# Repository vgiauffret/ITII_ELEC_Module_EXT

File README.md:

# ITII_ELEC_Module_EXT
Notre projet consiste à améliorer une ruche d’abeille en y ajoutant des capteurs pour permettre à un apiculteur d’obtenir différentes informations sur son ruché tel que la température, l’humidité et le poids de la ruche.

Toutes ces améliorations de la ruche ne doivent en aucun cas gêner l’apiculteur dans son travail et doivent permettre à la ruche de rester mobile. Le système doit être autonome.

Nous sommes en charges de créer le module externe de la Ruche. Le but du module externe de la ruche connecté est de gérer, d'enregistrer la visite de l'apiculteur et de transmettre les données relatives à l'entretien des ruches à une gateway. Le module devra fournir une IHM pour permettre à l'apiculteur d'interagir avec le système et de plusieurs capteurs permettant de récupérer les informations désirées.

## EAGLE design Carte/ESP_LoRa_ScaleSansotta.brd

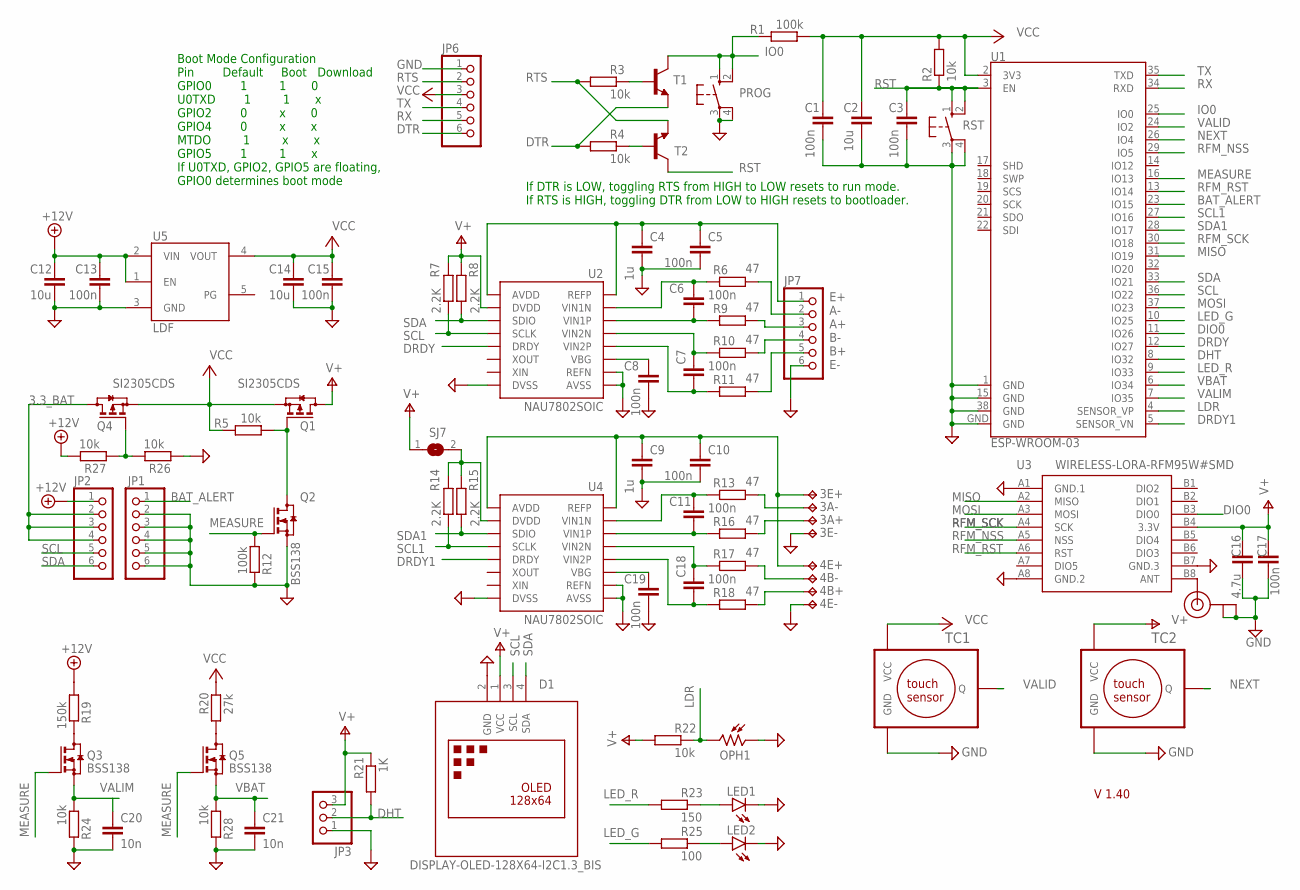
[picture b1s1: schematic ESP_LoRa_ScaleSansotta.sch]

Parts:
3A+, 3A-, 3E+, 3E-, 4B+, 4B-, 4E+, 4E-: TPTP17SQ; TP17SQ
C1, C3, C5, C6, C7, C8, C10, C11, C13, C15, C17, C18, C19: 100n; C1206
C2, C12, C14: 10u; C1210
C4, C9: 1u; C1210
C16: 4.7u; C1210
C20, C21: 10n; C1206
D1: DISPLAY-OLED-128X64-I2C1.3_BIS; DISPLAY-OLED-128X64-1.3-I2C_BIS
J1: U.FL
JP1, JP2, JP6, JP7: PINHD-1X6; 1X06
JP3: PINHD-1X3; 1X03
LED1, LED2: LEDSMT1206; 1206
OPH1: VT93N2; VT900
PROG: 10-XX; B3F-10XX
Q1, Q4: SI2305CDS; SOT23
Q2, Q3, Q5: BSS138; SOT23
R1, R12: 100k; R1206
R2, R3, R4, R5, R22, R24, R26, R27, R28: 10k; R1206
R6, R9, R10, R11, R13, R16, R17, R18: 47; R1206
R7, R8, R14, R15: 2.2K; R1206
R19: 150k; R1206
R20: 27k; R1206
R21: 1K; R1206
R23: 150; R1206
R25: 100; R1206
RST: 10-XX; B3F-10XX
SJ7: SJ
T1, T2: MMBT2222ALT1-NPN-SOT23-BEC; SOT23-BEC
TC1, TC2: TTP223R_H; TTP233RED_H
U1: ESP-WROOM-03
U2, U4: NAU7802SOIC; SO16
U3: WIRELESS-LORA-RFM95W#SMD
U5: LDF3.3; PPAK

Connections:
3.3_BAT: JP2.2, JP2.3, JP2.4, Q4.3 (D)
+12V: C12.1, C13.1, JP2.1, R19.1, R27.2, U5.1 (EN), U5.2 (VIN)
BAT_ALERT: JP1.1, U1.23 (IO15)
DHT: JP3.2, R21.1, U1.8 (IO32)
DIO0: U1.11 (IO26), U3.B3 (DIO0)
DRDY: U1.12 (IO27), U2.12 (DRDY)
DRDY1: U1.5 (SENSOR_VN), U4.12 (DRDY)
DTR: JP6.6, R4.1, T1.E
GND: 3E-.TP, 4E-.TP, C1.2, C2.2, C3.2, C4.2, C5.2, C8.2, C9.2, C10.2, C12.2, C13.2, C14.2, C15.2, C16.2, C17.2, C19.2, C20.2, C21.2, D1.2 (GND), J1.1 (GND), J1.2 (GND), JP1.2, JP1.3, JP1.4, JP1.5, JP1.6, JP3.1, JP6.1, JP7.6, LED1.C, LED2.C, OPH1.1, PROG.3, PROG.4 (P1), Q2.2 (S), R12.2, R24.2, R26.1, R28.2, RST.3, RST.4 (P1), TC1.P$3 (GND), TC2.P$3 (GND), U1.1 (GND), U1.15 (GND), U1.38 (GND), U1.GND, U2.7 (REFN), U2.8 (AVSS), U2.9 (DVSS), U3.A1 (GND.1), U3.A8 (GND.2), U3.B7 (GND.3), U4.7 (REFN), U4.8 (AVSS), U4.9 (DVSS), U5.3 (GND)
IO0: PROG.1 (S), PROG.2 (S1), R1.2, T1.C, U1.25 (IO0)
LDR: OPH1.2, R22.2, U1.4 (SENSOR_VP)
LED_G: R25.1, U1.10 (IO25)
LED_R: R23.1, U1.9 (IO33)
MEASURE: Q2.1 (G), Q3.1 (G), Q5.1 (G), R12.1, U1.16 (IO13)
MISO: U1.31 (IO19), U3.A2 (MISO)
MOSI: U1.37 (IO23), U3.A3 (MOSI)
unnamed: Q1.1 (G), Q2.3 (D), R5.1
unnamed: Q3.3 (D), R19.2
unnamed: J1.3 (SIGNAL), U3.B8 (ANT)
unnamed: R14.2, R15.2, SJ7.2, U4.15 (DVDD)
unnamed: Q5.3 (D), R20.1
unnamed: LED1.A, R23.2
unnamed: LED2.A, R25.2
unnamed: R3.2, T1.B
unnamed: JP7.2, R6.2
unnamed: R4.2, T2.B
unnamed: C8.1, U2.6 (VBG)
unnamed: C19.1, U4.6 (VBG)
unnamed: C11.2, R16.1, U4.3 (VIN1P)
unnamed: C11.1, R13.1, U4.2 (VIN1N)
unnamed: C6.2, R9.1, U2.3 (VIN1P)
unnamed: C6.1, R6.1, U2.2 (VIN1N)
unnamed: C7.1, R10.1, U2.4 (VIN2N)
unnamed: C7.2, R11.1, U2.5 (VIN2P)
unnamed: JP7.3, R9.2
unnamed: JP7.5, R11.2
unnamed: JP7.4, R10.2
unnamed: C18.1, R17.1, U4.4 (VIN2N)
unnamed: C18.2, R18.1, U4.5 (VIN2P)
unnamed: 4B+.TP, R18.2
unnamed: 4B-.TP, R17.2
unnamed: 3E+.TP, 4E+.TP, C9.1, C10.1, U4.1 (REFP), U4.16 (AVDD)
unnamed: 3A-.TP, R13.2
unnamed: 3A+.TP, R16.2
unnamed: C4.1, C5.1, JP7.1, U2.1 (REFP), U2.16 (AVDD)
unnamed: Q4.1 (G), R26.2, R27.1
NEXT: TC2.P$2 (Q), U1.26 (IO4)
RFM_NSS: U1.29 (IO5), U3.A5 (NSS)
RFM_RST: U1.13 (IO14), U3.A6 (RST)
RFM_SCK: U1.30 (IO18), U3.A4 (SCK)
RST: C3.1, R2.1, RST.1 (S), RST.2 (S1), T2.C, U1.3 (EN)
RTS: JP6.2, R3.1, T2.E
RX: JP6.5, U1.34 (RXD)
SCL: D1.3 (SCL), JP2.5, R7.1, U1.36 (IO22), U2.13 (SCLK)
SCL1: R14.1, U1.27 (IO16), U4.13 (SCLK)
SDA: D1.4 (SDA), JP2.6, R8.1, U1.33 (IO21), U2.14 (SDIO)
SDA1: R15.1, U1.28 (IO17), U4.14 (SDIO)
TX: JP6.4, U1.35 (TXD)
V+: C16.1, C17.1, D1.1 (VCC), JP3.3, Q1.3 (D), R7.2, R8.2, R21.2, R22.1, SJ7.1, TC2.P$1 (VCC), U2.15 (DVDD), U3.B4 (3.3V)
VALID: TC1.P$2 (Q), U1.24 (IO2)
VALIM: C20.1, Q3.2 (S), R24.1, U1.7 (IO35)
VBAT: C21.1, Q5.2 (S), R28.1, U1.6 (IO34)
VCC: C1.1, C2.1, C14.1, C15.1, JP6.3, Q1.2 (S), Q4.2 (S), R1.1, R2.2, R5.2, R20.2, TC1.P$1 (VCC), U1.2 (3V3), U5.4 (VOUT)

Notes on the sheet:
If DTR is LOW, toggling RTS from HIGH to LOW resets to run mode. If RTS is HIGH, toggling DTR from LOW to HIGH resets to bootloader.
Boot Mode Configuration Pin Default Boot Download GPIO0 1 1 0 U0TXD 1 1 x GPIO2 0 x 0 GPIO4 0 x x MTDO 1 x x GPIO5 1 1 x If U0TXD, GPIO2, GPIO5 are floating, GPIO0 determines boot mode
V 1.40
E+ A- A+ B- B+ E-

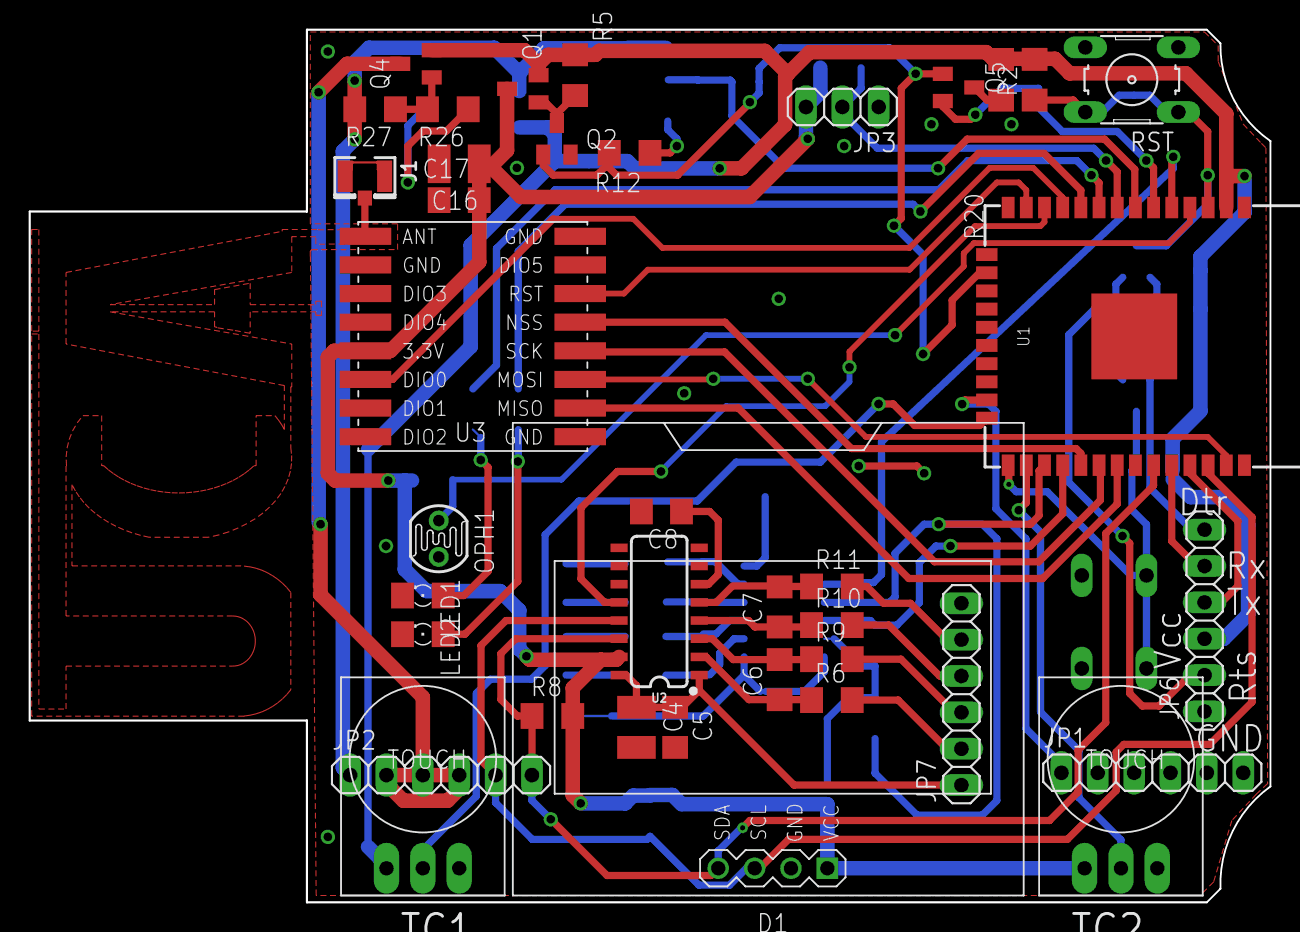
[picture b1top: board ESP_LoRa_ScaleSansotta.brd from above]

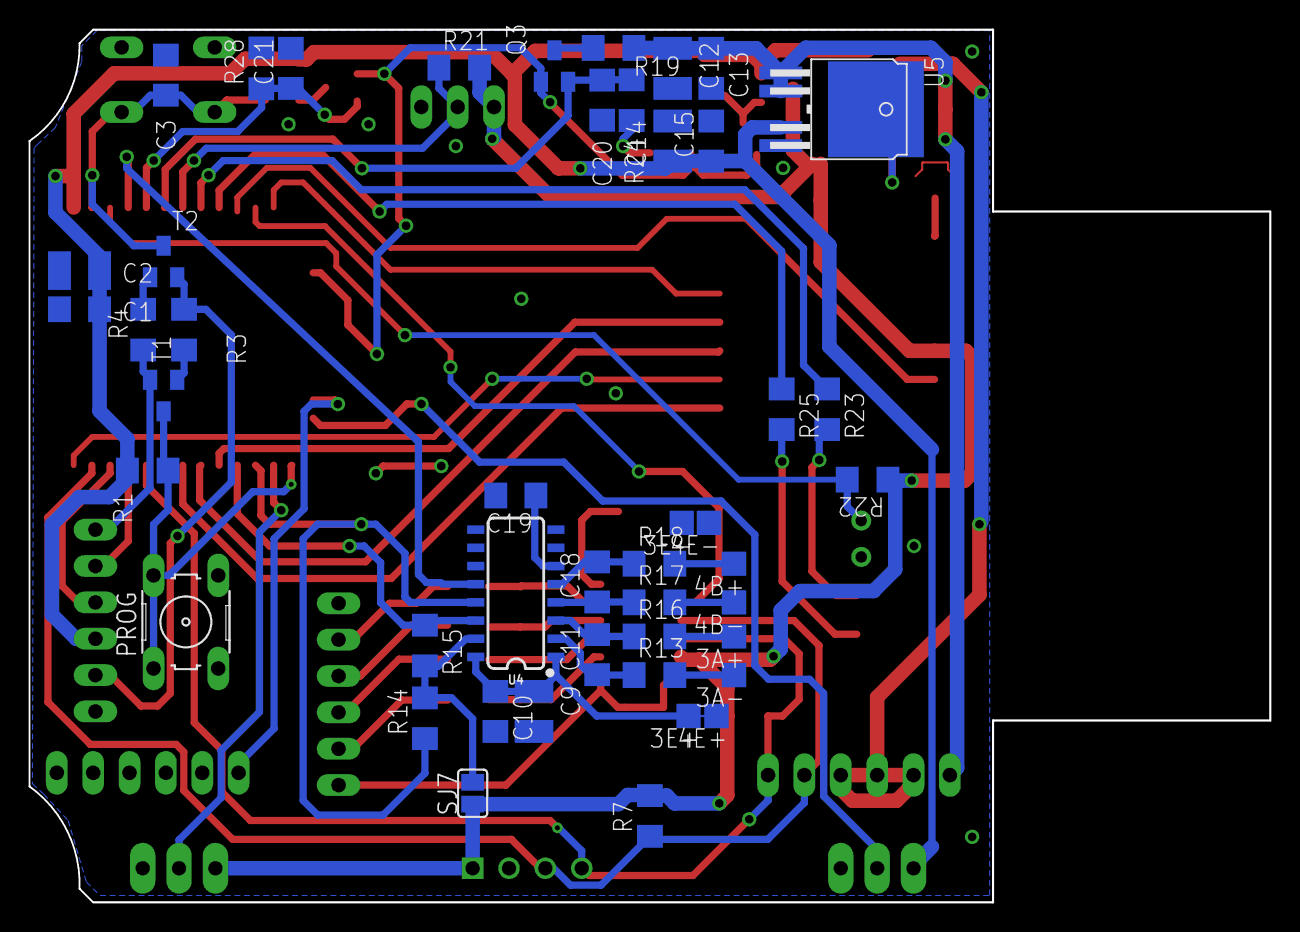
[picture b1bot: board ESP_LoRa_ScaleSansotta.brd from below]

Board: 2 copper layers, 86.7 x 61.0 mm, 84 parts (46 on the bottom side), 63 nets.

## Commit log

2019-11-08 Add Cahier des charges
    Fichier word qui contient le cahier des charges du module externe de la ruche connectée
2019-11-08 Ajout dossier taches de chaque eleves
2019-11-08 Bedoui_taches
    résumé des tâches effectués à chaque séance
2019-11-08 Taches
2019-11-08 Ajout planning
2020-01-20 Inventaire PInOut
2020-02-04 Présentation n°1
2020-02-07 Add files via upload
    présentation mi-module
2020-02-08 Code source
    Ajout du code qui fonctionne pour chaque élément
2020-02-08 Tableau d’assignation des Pins de l'ESP32
2020-04-17 Create PCB

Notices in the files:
parts and their libraries:
diy-modules: Released under the Creative Commons Attribution 4.0 International License: http://creativecommons.org/licenses/by/4.0
SparkFun-IC-Conversion: Licensing: Creative Commons ShareAlike 4.0 International - https://creativecommons.org/licenses/by-sa/4.0
